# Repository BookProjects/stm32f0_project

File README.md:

# stm32f0_project
Embedded Systems Project for the STM32F0

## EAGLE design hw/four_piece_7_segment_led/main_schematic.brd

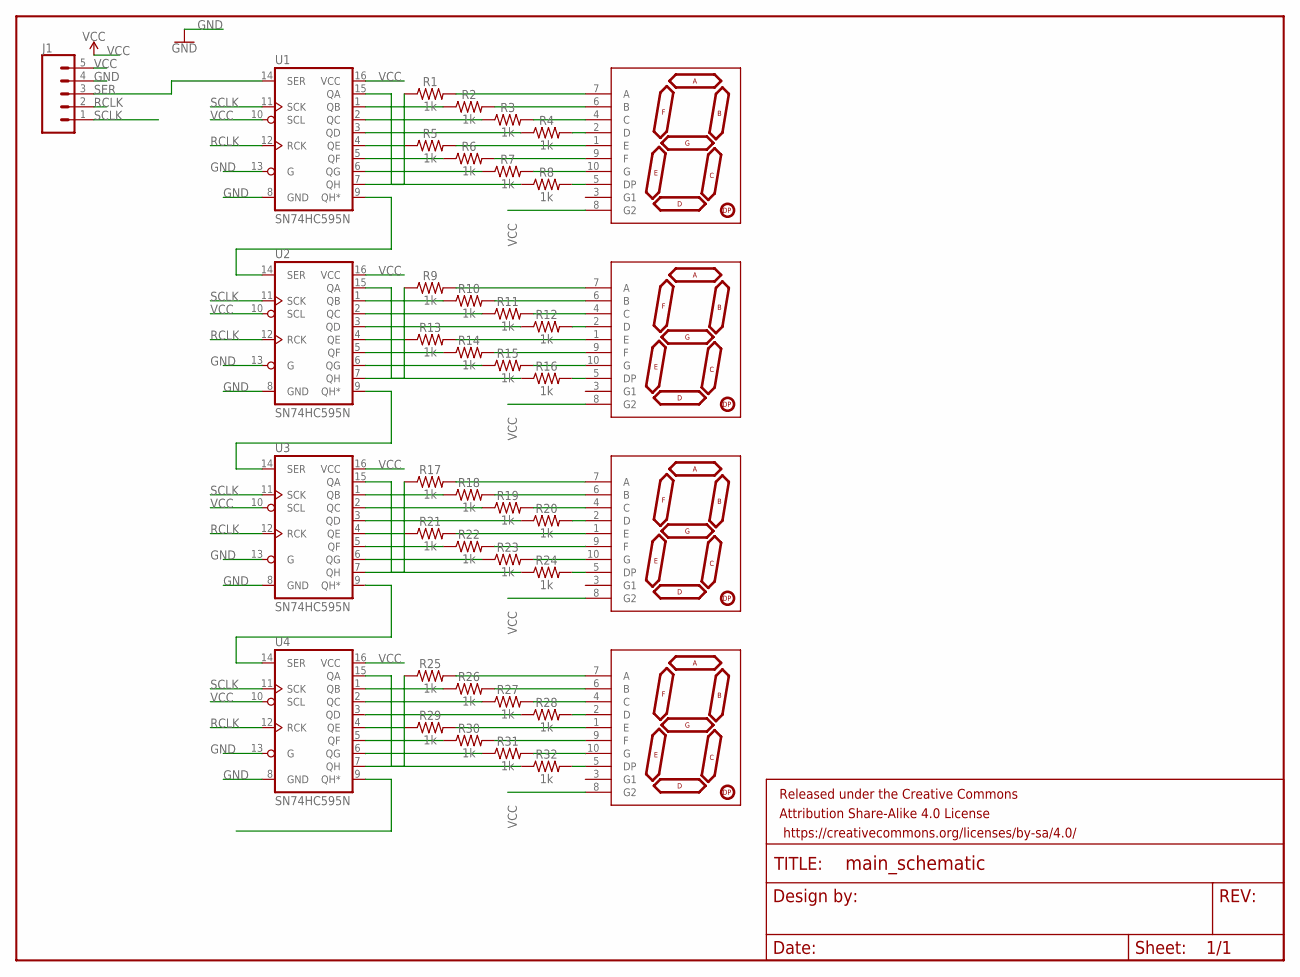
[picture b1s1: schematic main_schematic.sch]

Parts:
FRAME1: FRAME-LETTER; CREATIVE_COMMONS
J1: CONN_05; 1X05
R1, R2, R3, R4, R5, R6, R7, R8, R9, R10, R11, R12, R13, R14, R15, R16, R17, R18, R19, R20, R21, R22, R23, R24, R25, R26, R27, R28, R29, R30, R31, R32: 1k; AXIAL-0.3-KIT
U1, U2, U3, U4: SN74HC595N; DIP16
U$1, U$2, U$3, U$4: YSD-160AB3C-8; 7-SEGMENT-1"PTH-EZ

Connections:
GND: J1.4, U1.8 (GND), U1.13 (G), U2.8 (GND), U2.13 (G), U3.8 (GND), U3.13 (G), U4.8 (GND), U4.13 (G)
unnamed: R7.P$1 (1), U1.6 (QG)
unnamed: R2.P$1 (1), U1.1 (QB)
unnamed: R8.P$2 (2), U$1.5 (DP)
unnamed: R3.P$1 (1), U1.2 (QC)
unnamed: R4.P$1 (1), U1.3 (QD)
unnamed: R7.P$2 (2), U$1.10 (G)
unnamed: R6.P$2 (2), U$1.9 (F)
unnamed: R5.P$2 (2), U$1.1 (E)
unnamed: R4.P$2 (2), U$1.2 (D)
unnamed: R3.P$2 (2), U$1.4 (C)
unnamed: R2.P$2 (2), U$1.6 (B)
unnamed: R1.P$2 (2), U$1.7 (A)
unnamed: R5.P$1 (1), U1.4 (QE)
unnamed: R6.P$1 (1), U1.5 (QF)
unnamed: R8.P$1 (1), U1.15 (QA)
unnamed: R1.P$1 (1), U1.7 (QH)
unnamed: U1.9 (QH*), U2.14 (SER)
unnamed: R16.P$2 (2), U$2.5 (DP)
unnamed: R15.P$2 (2), U$2.10 (G)
unnamed: R14.P$2 (2), U$2.9 (F)
unnamed: R13.P$2 (2), U$2.1 (E)
unnamed: R12.P$2 (2), U$2.2 (D)
unnamed: R11.P$2 (2), U$2.4 (C)
unnamed: R10.P$2 (2), U$2.6 (B)
unnamed: U2.9 (QH*), U3.14 (SER)
unnamed: R9.P$2 (2), U$2.7 (A)
unnamed: R10.P$1 (1), U2.1 (QB)
unnamed: R11.P$1 (1), U2.2 (QC)
unnamed: R12.P$1 (1), U2.3 (QD)
unnamed: R13.P$1 (1), U2.4 (QE)
unnamed: R14.P$1 (1), U2.5 (QF)
unnamed: R15.P$1 (1), U2.6 (QG)
unnamed: R9.P$1 (1), U2.7 (QH)
unnamed: R16.P$1 (1), U2.15 (QA)
unnamed: R24.P$2 (2), U$3.5 (DP)
unnamed: R23.P$2 (2), U$3.10 (G)
unnamed: R22.P$2 (2), U$3.9 (F)
unnamed: R21.P$2 (2), U$3.1 (E)
unnamed: R20.P$2 (2), U$3.2 (D)
unnamed: R19.P$2 (2), U$3.4 (C)
unnamed: R18.P$2 (2), U$3.6 (B)
unnamed: U3.9 (QH*), U4.14 (SER)
unnamed: R17.P$2 (2), U$3.7 (A)
unnamed: R18.P$1 (1), U3.1 (QB)
unnamed: R19.P$1 (1), U3.2 (QC)
unnamed: R20.P$1 (1), U3.3 (QD)
unnamed: R21.P$1 (1), U3.4 (QE)
unnamed: R22.P$1 (1), U3.5 (QF)
unnamed: R23.P$1 (1), U3.6 (QG)
unnamed: R17.P$1 (1), U3.7 (QH)
unnamed: R24.P$1 (1), U3.15 (QA)
unnamed: R32.P$2 (2), U$4.5 (DP)
unnamed: R31.P$2 (2), U$4.10 (G)
unnamed: R30.P$2 (2), U$4.9 (F)
unnamed: R29.P$2 (2), U$4.1 (E)
unnamed: R28.P$2 (2), U$4.2 (D)
unnamed: R27.P$2 (2), U$4.4 (C)
unnamed: R26.P$2 (2), U$4.6 (B)
unnamed: R25.P$2 (2), U$4.7 (A)
unnamed: R26.P$1 (1), U4.1 (QB)
unnamed: R27.P$1 (1), U4.2 (QC)
unnamed: R28.P$1 (1), U4.3 (QD)
unnamed: R29.P$1 (1), U4.4 (QE)
unnamed: R30.P$1 (1), U4.5 (QF)
unnamed: R31.P$1 (1), U4.6 (QG)
unnamed: R25.P$1 (1), U4.7 (QH)
unnamed: R32.P$1 (1), U4.15 (QA)
RCLK: J1.2, U1.12 (RCK), U2.12 (RCK), U3.12 (RCK), U4.12 (RCK)
SCLK: J1.1, U1.11 (SCK), U2.11 (SCK), U3.11 (SCK), U4.11 (SCK)
SER: J1.3, U1.14 (SER)
VCC: J1.5, U1.10 (SCL), U1.16 (VCC), U2.10 (SCL), U2.16 (VCC), U3.10 (SCL), U3.16 (VCC), U4.10 (SCL), U4.16 (VCC), U$1.8 (G2), U$2.8 (G2), U$3.8 (G2), U$4.8 (G2)

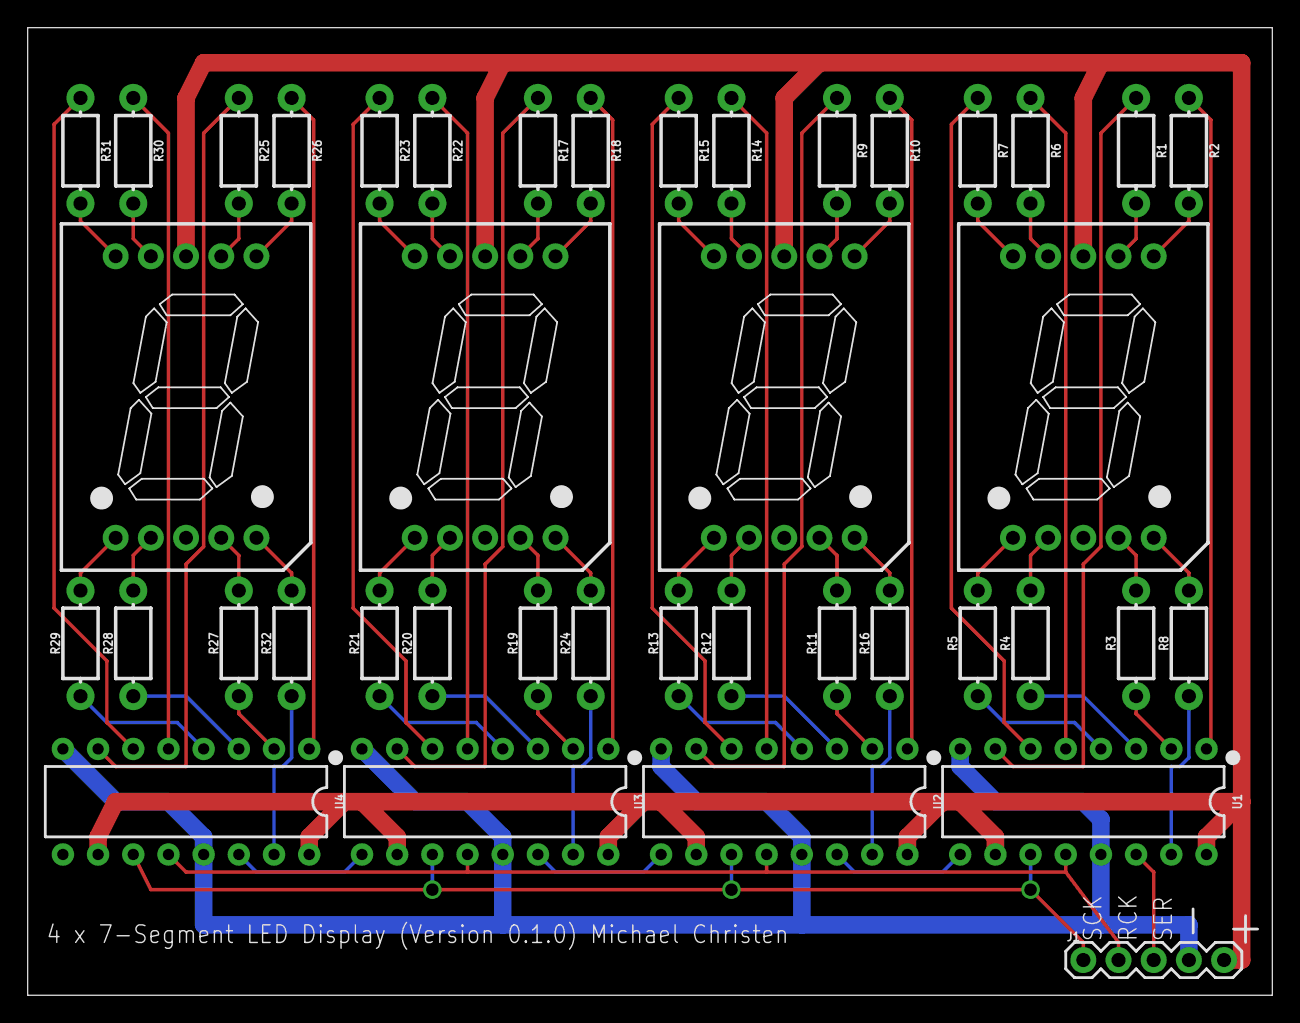
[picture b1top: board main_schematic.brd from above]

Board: 2 copper layers, 89.8 x 69.8 mm, 42 parts (0 on the bottom side), 72 nets.

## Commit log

2017-01-07 Adding stm32f0 discovery firmware unadulterated
2017-01-07 Cleanup third party STM32F0 code for our use case * remove extraneous toolchain setup * dos2unix conversion
2017-01-07 Get working Makefile, even though it's ugly
2017-01-07 Fix compilation issues with third party
2017-01-08 Extend Makefile & add doc:
    * cleanup
    * add flashing commands
    * add help
    * turn off listings by default to speed compilation and remove verbosity
    * run through examples
2017-01-08 Get working example of uart
2017-01-23 Make bad usart module
2017-01-23 Enable sending ints as string over uart
2017-01-25 Get delay working
2017-01-31 update .gitignore wit vim swap files
2017-01-31 Get working synchronous example using PWM example
2017-01-31 Add clarifying comments
2017-01-31 Clean up
2017-02-20 Get example of IO driven LED7 working
2017-02-20 Allow system configuration to not occur on a per example basis
2017-02-20 Remove all other configuration
2017-02-20 Incorporate timing into configuration
2017-02-20 cleanup led7
2017-02-20 Added .editorconfig
2017-02-20 Fix indentations
2017-02-20 Add header guards and c linkage
2017-02-21 keep Makefile echo statement extra space
2017-02-21 Break out mcu specific variables into included Makefile
2017-02-21 Move definitions around in Makefiles
2017-02-21 Simplifying Makefile
2017-02-21 Cleaning up print statements and variables
2017-02-21 Fix cross compiler flags
2017-02-21 Move cmd variable definitions above make cmds
2017-02-21 Get basic native sw compiling
2017-02-21 Split up Makefile even more and add namespace
2017-02-21 Configure unity test cases
2017-02-21 Get an actual test
2017-02-22 Install cross compiler locally (problem with it always installing)
2017-02-26 Finish
2018-11-07 Add hw

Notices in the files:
parts and their libraries:
SparkFun-Aesthetics: Licensing: Creative Commons ShareAlike 4.0 International - https://creativecommons.org/licenses/by-sa/4.0
SparkFun-Aesthetics: Released under the Creative Commons Attribution Share-Alike 4.0 License
SparkFun-Aesthetics: https://creativecommons.org/licenses/by-sa/4.0
